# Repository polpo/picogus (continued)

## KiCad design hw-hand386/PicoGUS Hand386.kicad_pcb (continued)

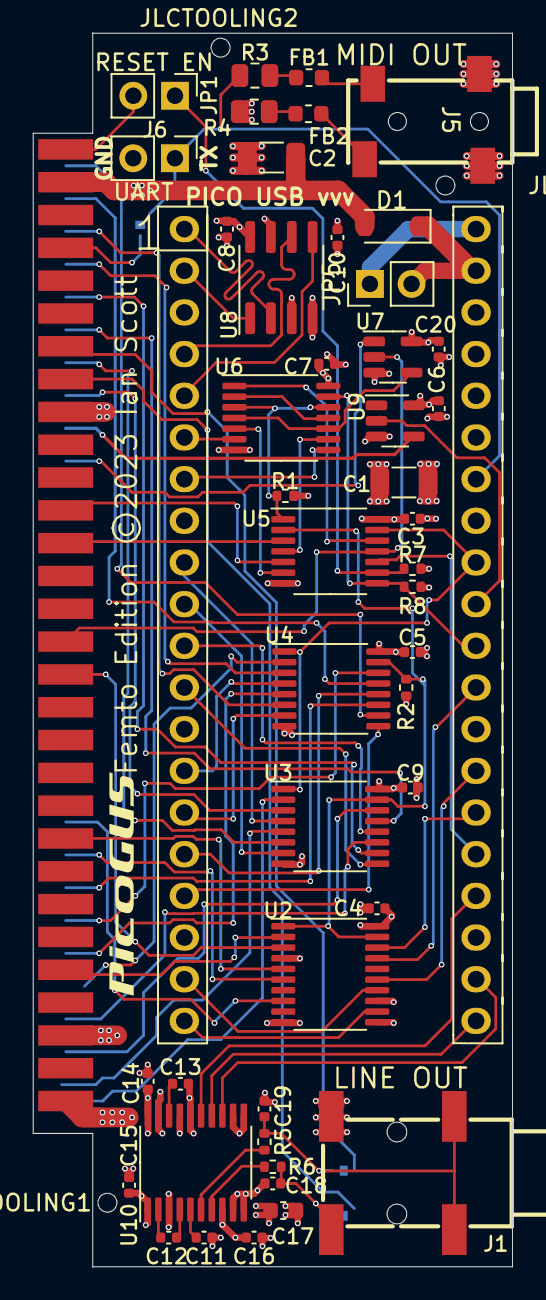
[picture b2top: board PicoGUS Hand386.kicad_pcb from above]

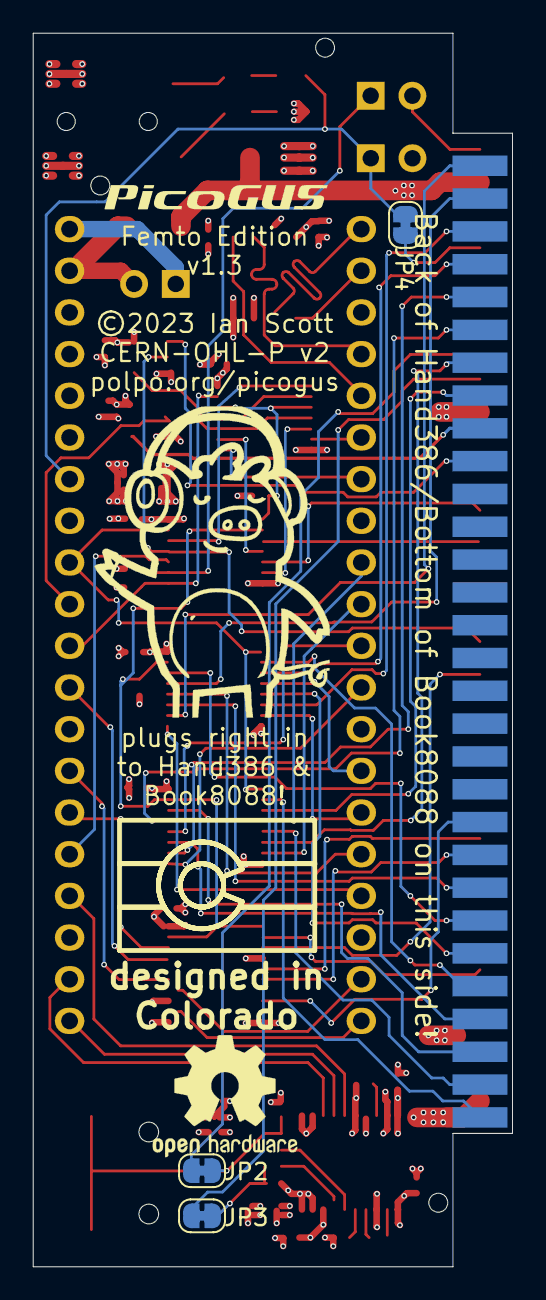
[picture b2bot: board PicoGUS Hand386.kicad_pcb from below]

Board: 4 copper layers, 29.2 x 75.2 mm, 53 parts (3 on the bottom side), 82 nets.

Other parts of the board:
JLCTOOLING1, JLCTOOLING2, JLCTOOLING3: JLCPCB-tooling

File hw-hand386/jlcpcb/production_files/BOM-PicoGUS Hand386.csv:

Comment,Designator,Footprint,LCSC
1K,R8,R_0402_1005Metric,C11702
2.2uF,"C11,C12",C_0402_1005Metric,C12530
PCM5100,U10,TSSOP-20_4.4x6.5mm_P0.65mm,C131154
74AHC14,U5,TSSOP-14_4.4x5mm_P0.65mm,C138310
0.1uF,"C13,C14,C15,C16,C20,C3,C4,C5,C6,C7,C8,C9",C_0402_1005Metric,C1525
SN74CB3T3245,U2,TSSOP-20_4.4x6.5mm_P0.65mm,C15298
2.2nF,"C18,C19",C_0402_1005Metric,C1531
33,R4,R_0805_2012Metric,C161967
10uF,C17,C_0603_1608Metric,C19702
470,"R5,R6",R_0402_1005Metric,C25117
10K,"R1,R2,R7",R_0402_1005Metric,C25744
APS6404L-3SQN-SN,U8,SOIC-8_3.9x4.9mm_P1.27mm,C3028887
1K @ 100MHz,"FB1,FB2",L_0603_1608Metric,C50069
1uF,C10,C_0402_1005Metric,C52923
SN74CB3T3257,"U3,U4",TSSOP-16_4.4x5mm_P0.65mm,C544573
AudioJack3,J5,PJ-231F-4A,C707219
10,R3,R_0805_2012Metric,C728003
74LVC00,U6,TSSOP-14_4.4x5mm_P0.65mm,C7803
74LVC1G00,U7,SOT-23-5,C7826
74LVC1G06,U9,SOT-23-5,C840103
1A 20V Schottky,D1,D_SOD-123,C8598
AudioJack3,J1,PJ-321A,C879743
47uF,"C1,C2",C_1206_3216Metric,C96123
Bus_ISA_8bit,J3,EDGE-60,

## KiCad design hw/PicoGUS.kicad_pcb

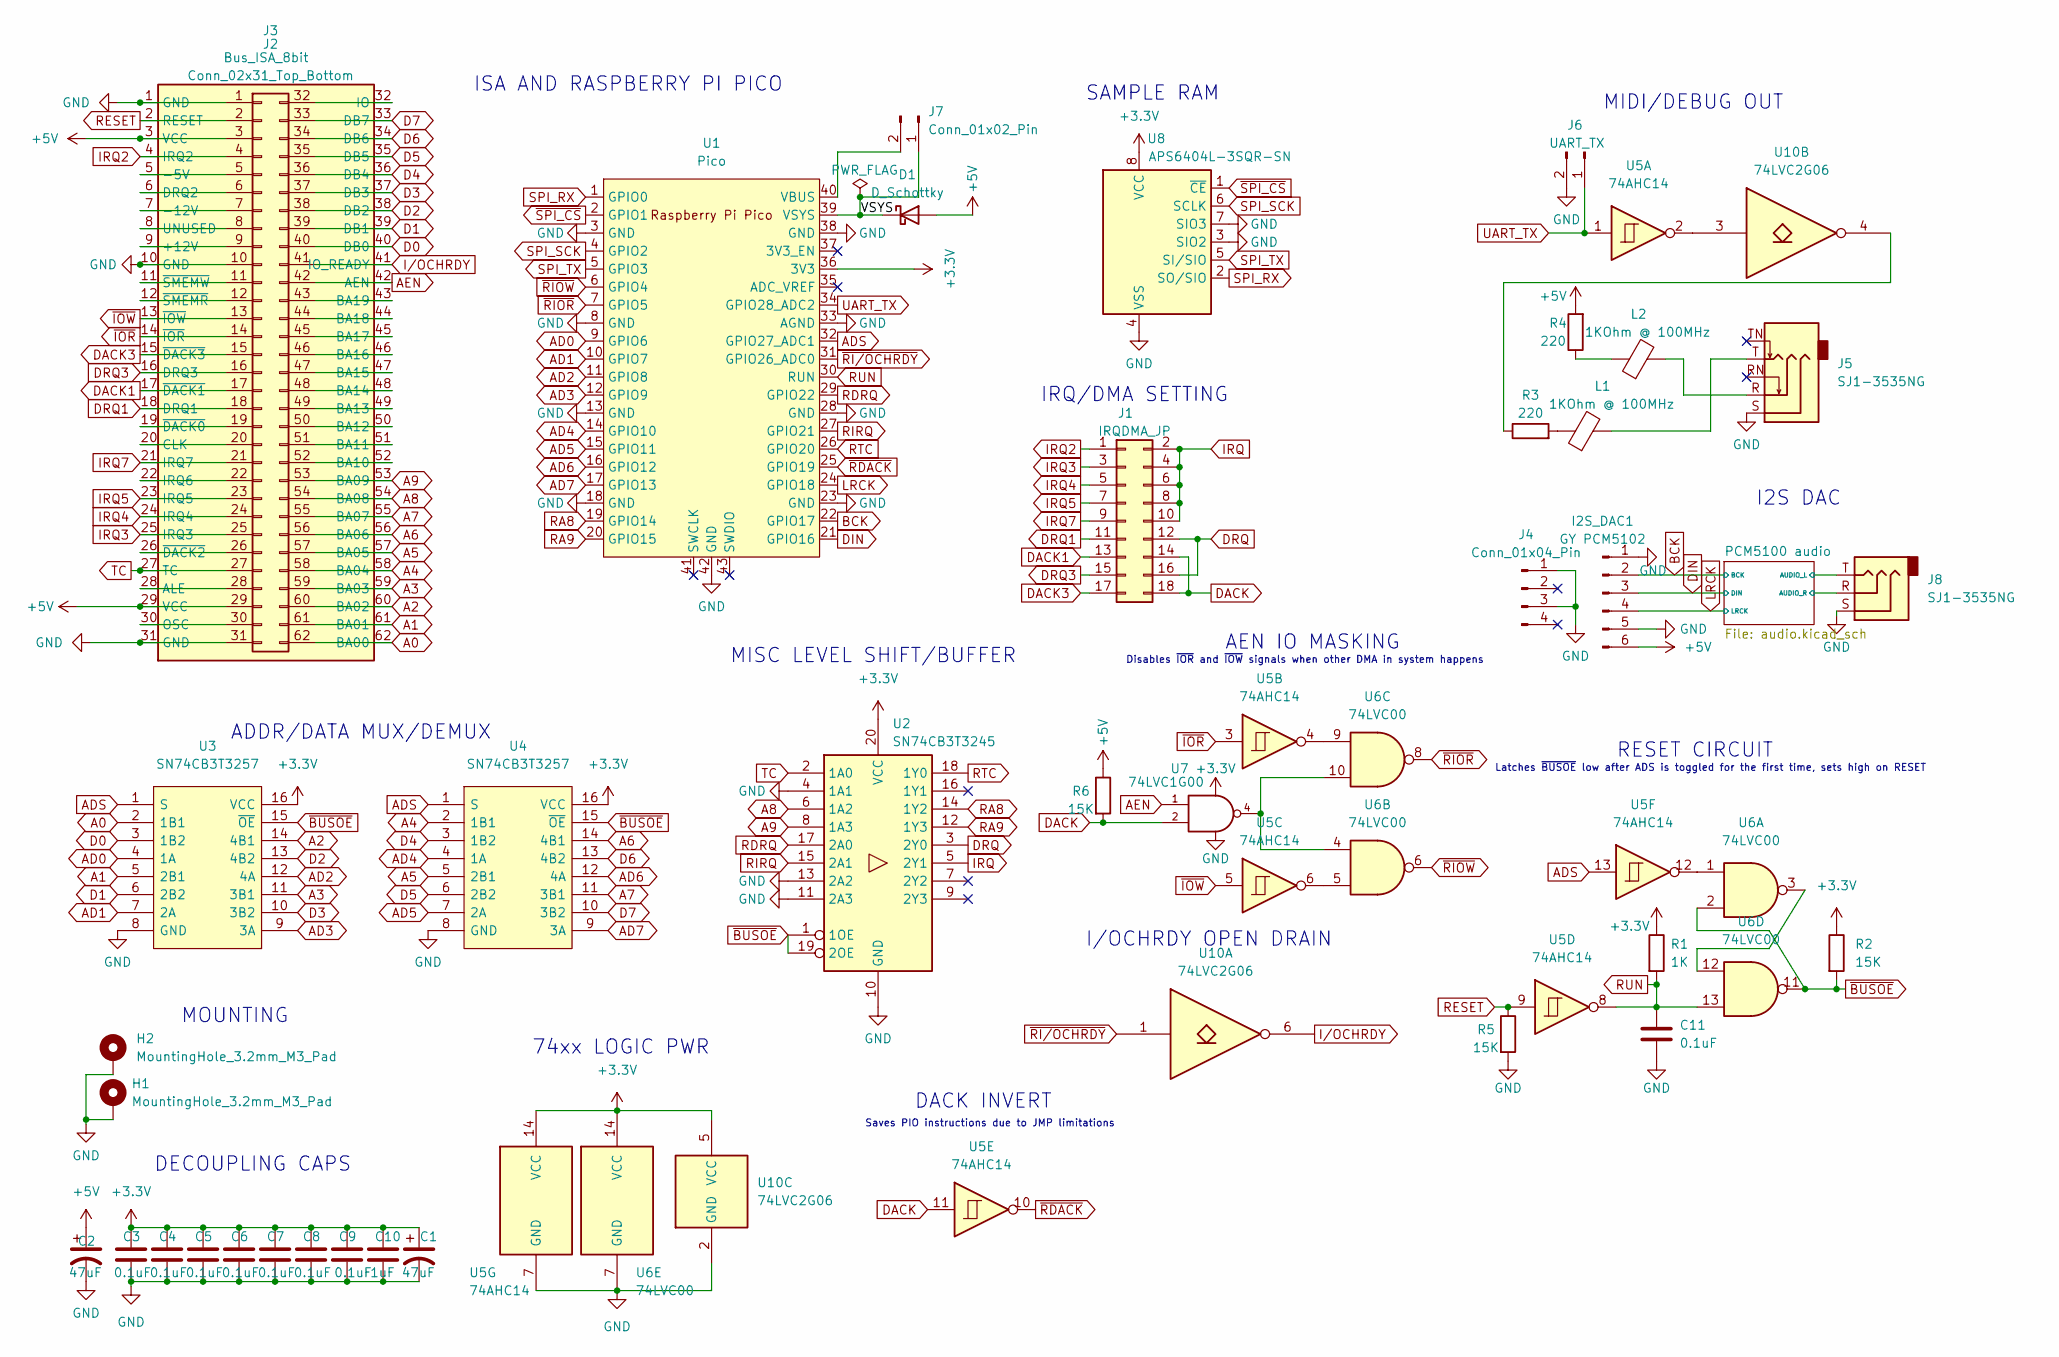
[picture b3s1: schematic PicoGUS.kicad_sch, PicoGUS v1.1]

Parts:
C1, C2: 47uF; C_1206_3216Metric; LCSC C96123
C3, C4, C5, C6, C7, C8, C9, C11: 0.1uF; C_0805_2012Metric; LCSC C49678
C10: 1uF; C_0805_2012Metric; LCSC C28323
D1: D_Schottky; D_SOD-123; LCSC C8598
H1, H2: MountingHole_3.2mm_M3_Pad
I2S_DAC1: GY PCM5102; PinHeader_1x06_P2.54mm_Vertical
J1: IRQDMA_JP; PinHeader_2x09_P2.54mm_Vertical; LCSC C492426
J2: Conn_02x31_Top_Bottom; PinHeader_2x31_P2.54mm_Vertical
J3: Bus_ISA_8bit; BUS_PC_chamfer
J4: Conn_01x04_Pin; PinHeader_1x04_P2.54mm_Vertical
J5, J8: SJ1-3535NG; Jack_3.5mm_CUI_SJ1-3535NG_Horizontal; LCSC C2910528
J6: UART_TX; PinHeader_1x02_P2.54mm_Vertical
J7: Conn_01x02_Pin; PinHeader_1x02_P2.54mm_Vertical
L1, L2: 1KOhm @ 100MHz; L_0805_2012Metric; LCSC C1017
R1: 1K; R_0805_2012Metric; LCSC C17513
R2, R5, R6: 15K; R_0805_2012Metric; LCSC C17475
R3, R4: 220; R_0805_2012Metric; LCSC C5120092
U1: Pico; RPi_Pico_SMD_TH; LCSC C2905423
U2: SN74CB3T3245; TSSOP-20_4.4x6.5mm_P0.65mm; LCSC C15298
U3, U4: SN74CB3T3257; TSSOP-16_4.4x5mm_P0.65mm; Manufacturer_Part_Number 74FST3257DR2G; Mouser Part Number 863-74FST3257DR2G
U5: 74AHC14; SOIC-14_3.9x8.7mm_P1.27mm; LCSC C5510
U6: 74LVC00; SOIC-14_3.9x8.7mm_P1.27mm; LCSC C7802
U7: 74LVC1G00; SOT-23-5; LCSC C7826
U8: APS6404L-3SQR-SN; SOIC-8_3.9x4.9mm_P1.27mm; LCSC C139966
U10: 74LVC2G06; TSOP-6_1.65x3.05mm_P0.95mm; LCSC C548558

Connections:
+5V: C2.1, D1.2 (A), I2S_DAC1.6, J2.3, J2.29, J3.3 (VCC), J3.29 (VCC), R4.2, R6.1
/PCM5100 audio/AUDIO_L: J8.T; also elsewhere on the board
/PCM5100 audio/AUDIO_R: J8.R; also elsewhere on the board
/VSYS: D1.1 (K), J7.1, U1.39 (VSYS)
A0: J2.62, J3.62 (BA00), U3.2 (1B1)
A1: J2.61, J3.61 (BA01), U3.5 (2B1)
A2: J2.60, J3.60 (BA02), U3.14 (4B1)
A3: J2.59, J3.59 (BA03), U3.11 (3B1)
A4: J2.58, J3.58 (BA04), U4.2 (1B1)
A5: J2.57, J3.57 (BA05), U4.5 (2B1)
A6: J2.56, J3.56 (BA06), U4.14 (4B1)
A7: J2.55, J3.55 (BA07), U4.11 (3B1)
A8: J2.54, J3.54 (BA08), U2.6 (1A2)
A9: J2.53, J3.53 (BA09), U2.8 (1A3)
AD0: U1.9 (GPIO6), U3.4 (1A)
AD1: U1.10 (GPIO7), U3.7 (2A)
AD2: U1.11 (GPIO8), U3.12 (4A)
AD3: U1.12 (GPIO9), U3.9 (3A)
AD4: U1.14 (GPIO10), U4.4 (1A)
AD5: U1.15 (GPIO11), U4.7 (2A)
AD6: U1.16 (GPIO12), U4.12 (4A)
AD7: U1.17 (GPIO13), U4.9 (3A)
ADS: U1.32 (GPIO27_ADC1), U3.1 (S), U4.1 (S), U5.13
AEN: J2.42, J3.42 (AEN), U7.1
BCK: I2S_DAC1.2, U1.22 (GPIO17); also elsewhere on the board
D0: J2.40, J3.40 (DB0), U3.3 (1B2)
D1: J2.39, J3.39 (DB1), U3.6 (2B2)
D2: J2.38, J3.38 (DB2), U3.13 (4B2)
D3: J2.37, J3.37 (DB3), U3.10 (3B2)
D4: J2.36, J3.36 (DB4), U4.3 (1B2)
D5: J2.35, J3.35 (DB5), U4.6 (2B2)
D6: J2.34, J3.34 (DB6), U4.13 (4B2)
D7: J2.33, J3.33 (DB7), U4.10 (3B2)
DACK: J1.14, J1.18, R6.2, U5.11, U7.2
DACK1: J1.13, J2.17, J3.17 (~DACK1)
DACK3: J1.17, J2.15, J3.15 (~DACK3)
DIN: I2S_DAC1.3, U1.21 (GPIO16); also elsewhere on the board
DRQ: J1.12, J1.16, U2.3 (2Y0)
DRQ1: J1.11, J2.18, J3.18 (DRQ1)
DRQ3: J1.15, J2.16, J3.16 (DRQ3)
GND: C1.2, C2.2, C3.2, C4.2, C5.2, C6.2, C7.2, C8.2, C9.2, C10.2, C11.2, H1.1, H2.1, I2S_DAC1.1, I2S_DAC1.5, J2.1, J2.10, J2.31, J3.1 (GND), J3.10 (GND), J3.31 (GND), J4.1, J4.3, J5.S, J6.2, J8.S, R5.2, U1.3 (GND), U1.8 (GND), U1.13 (GND), U1.18 (GND), U1.23 (GND), U1.28 (GND), U1.33 (AGND), U1.38 (GND), U1.42 (GND), U2.4 (1A1), U2.10 (GND), U2.11 (2A3), U2.13 (2A2), U3.8 (GND), U4.8 (GND), U5.7 (GND), U6.7 (GND), U7.3 (GND), U8.3 (SIO2), U8.4 (VSS), U8.7 (SIO3), U10.2 (GND); also elsewhere on the board
IRQ: J1.2, J1.4, J1.6, J1.8, J1.10, U2.5 (2Y1)
IRQ2: J1.1, J2.4, J3.4 (IRQ2)
IRQ3: J1.3, J2.25, J3.25 (IRQ3)
IRQ4: J1.5, J2.24, J3.24 (IRQ4)
IRQ5: J1.7, J2.23, J3.23 (IRQ5)
IRQ7: J1.9, J2.21, J3.21 (IRQ7)
I/OCHRDY: J2.41, J3.41 (IO_READY), U10.6
LRCK: I2S_DAC1.4, U1.24 (GPIO18); also elsewhere on the board
unnamed: J2.5, J3.5 (-5V)
unnamed: J2.6, J3.6 (DRQ2)
unnamed: J2.7, J3.7 (-12V)
unnamed: J2.8, J3.8 (UNUSED)
unnamed: J2.9, J3.9 (+12V)
unnamed: J2.11, J3.11 (~SMEMW)
unnamed: J2.12, J3.12 (~SMEMR)
unnamed: J2.19, J3.19 (~DACK0)
unnamed: J2.20, J3.20 (CLK)
unnamed: J2.22, J3.22 (IRQ6)
unnamed: J2.26, J3.26 (~DACK2)
unnamed: J2.28, J3.28 (ALE)
unnamed: J2.30, J3.30 (OSC)
unnamed: J2.32, J3.32 (IO)
unnamed: J2.43, J3.43 (BA19)
unnamed: J2.44, J3.44 (BA18)
unnamed: J2.45, J3.45 (BA17)
unnamed: J2.46, J3.46 (BA16)
unnamed: J2.47, J3.47 (BA15)
unnamed: J2.48, J3.48 (BA14)
unnamed: J2.49, J3.49 (BA13)
unnamed: J2.50, J3.50 (BA12)
unnamed: J2.51, J3.51 (BA11)
unnamed: J2.52, J3.52 (BA10)
unnamed: J5.R, L2.2
unnamed: J5.T, L1.2
unnamed: J7.2, U1.40 (VBUS)
unnamed: L1.1, R3.2
unnamed: L2.1, R4.1
unnamed: R3.1, U10.4
unnamed: U5.4, U6.9
unnamed: U5.6, U6.5
unnamed: U5.12, U6.1
unnamed: U6.4, U6.10, U7.4
unnamed: U6.3, U6.12
unnamed: U5.2, U10.3
RA8: U1.19 (GPIO14), U2.14 (1Y2)
RA9: U1.20 (GPIO15), U2.12 (1Y3)
RDRQ: U1.29 (GPIO22), U2.17 (2A0)
RESET: J2.2, J3.2 (RESET), R5.1, U5.9
RIRQ: U1.27 (GPIO21), U2.15 (2A1)
RTC: U1.26 (GPIO20), U2.18 (1Y0)
RUN: C11.1, R1.2, U1.30 (RUN), U5.8, U6.13
SPI_RX: U1.1 (GPIO0), U8.2 (SO/SIO)
SPI_SCK: U1.4 (GPIO2), U8.6 (SCLK)
SPI_TX: U1.5 (GPIO3), U8.5 (SI/SIO)
TC: J2.27, J3.27 (TC), U2.2 (1A0)
UART_TX: J6.1, U1.34 (GPIO28_ADC2), U5.1
~BUSOE: R2.2, U2.1 (1OE), U2.19 (2OE), U3.15 (~OE), U4.15 (~OE), U6.2, U6.11
~IOR: J2.14, J3.14 (~IOR), U5.3
~IOW: J2.13, J3.13 (~IOW), U5.5
~RDACK: U1.25 (GPIO19), U5.10
~RIOR: U1.7 (GPIO5), U6.8
~RIOW: U1.6 (GPIO4), U6.6
~RI/OCHRDY: U1.31 (GPIO26_ADC0), U10.1
~SPI_CS: U1.2 (GPIO1), U8.1 (~CE)

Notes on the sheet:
Saves PIO instructions due to JMP limitations
DECOUPLING CAPS
I2S DAC
Disables ~{IOR} and ~{IOW} signals when other DMA in system happens
Latches ~{BUSOE} low after ADS is toggled for the first time, sets high on RESET
MIDI/DEBUG OUT
MOUNTING
MISC LEVEL SHIFT/BUFFER
IRQ/DMA SETTING
DACK INVERT
ADDR/DATA MUX/DEMUX
SAMPLE RAM
AEN IO MASKING
ISA AND RASPBERRY PI PICO
RESET CIRCUIT
I/OCHRDY OPEN DRAIN
74xx LOGIC PWR

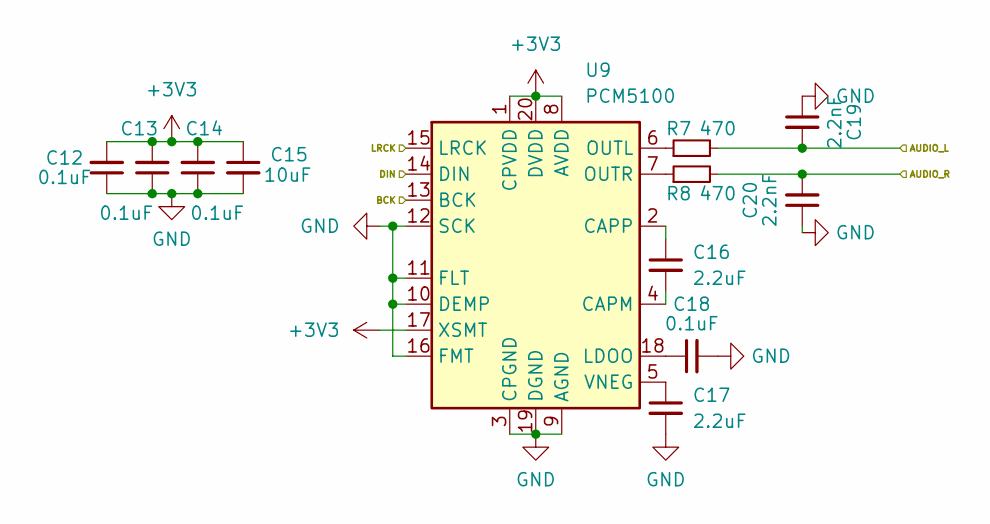
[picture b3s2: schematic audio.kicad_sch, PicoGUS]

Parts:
C12, C13, C14, C18: 0.1uF; C_0805_2012Metric
C15: 10uF; C_0805_2012Metric
C16, C17: 2.2uF; C_0805_2012Metric
C19, C20: 2.2nF; C_0805_2012Metric
R7, R8: 470; R_0805_2012Metric
U9: PCM5100; TSSOP-20_4.4x6.5mm_P0.65mm

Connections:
/PCM5100 audio/AUDIO_L: C19.2, R7.2; also elsewhere on the board
/PCM5100 audio/AUDIO_R: C20.2, R8.2; also elsewhere on the board
BCK: U9.13 (BCK); also elsewhere on the board
DIN: U9.14 (DIN); also elsewhere on the board
GND: C12.1, C13.1, C14.1, C15.2, C17.2, C18.2, C19.1, C20.1, U9.3 (CPGND), U9.9 (AGND), U9.10 (DEMP), U9.11 (FLT), U9.12 (SCK), U9.16 (FMT), U9.19 (DGND); also elsewhere on the board
LRCK: U9.15 (LRCK); also elsewhere on the board
unnamed: C16.2, U9.4 (CAPM)
unnamed: C16.1, U9.2 (CAPP)
unnamed: C18.1, U9.18 (LDOO)
unnamed: R7.1, U9.6 (OUTL)
unnamed: R8.1, U9.7 (OUTR)
unnamed: C17.1, U9.5 (VNEG)

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
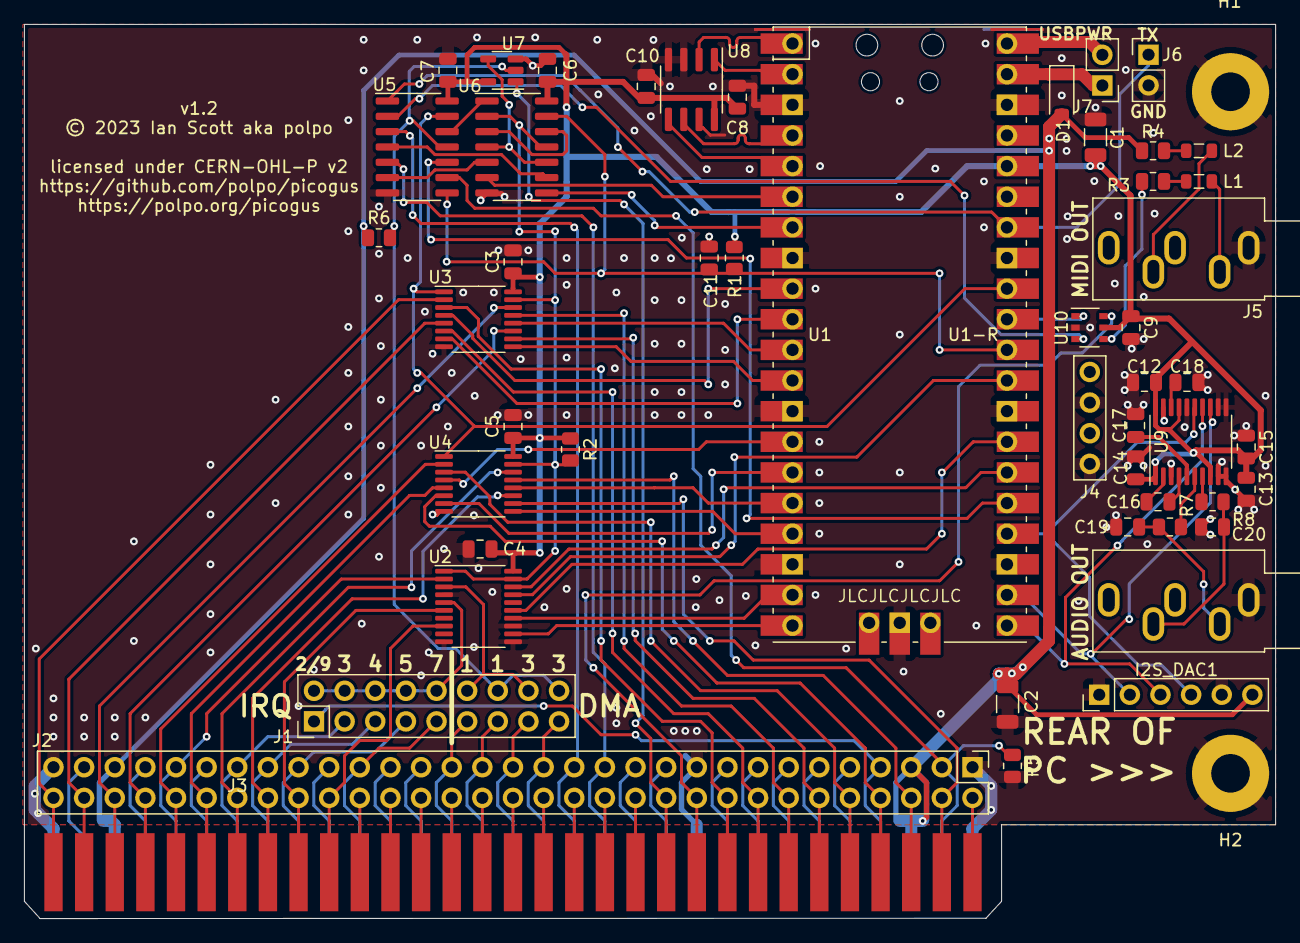
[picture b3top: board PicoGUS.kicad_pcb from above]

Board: 2 copper layers, 103.7 x 74.1 mm, 53 parts (0 on the bottom side), 112 nets.

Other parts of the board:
U1-R: GHOST-20P; Ghost-20P

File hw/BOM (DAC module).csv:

Mfr. #,Manufacturer,Qty,Mouser #,Digi-Key #,LCSC #,Customer #,Footprint,Description,Notes
CL31A476MPHNNNE,Samsung Electro-Mechanics ,2,187-CL31A476MPHNNNE,1276-3063-1-ND,C96123,"C1,C2",0805,47 µF ±20% 10V Ceramic Capacitor X5R 1206 (3216 Metric),Subst any 47uF electrolytic cap w/ 2mm lead spacing
CL21B105KBFNNNE,Samsung Electro-Mechanics ,1,187-CL21B105KBFNNNE,1276-1029-1-ND,C28323,C10,0805,1 µF ±10% 50V Ceramic Capacitor X7R 0805 (2012 Metric),Subst any X7R 1uF 0805 ceramic cap
CL21B104KCFNNNE,Samsung Electro-Mechanics ,8,187-CL21B104KCFNNNE,399-C0805C104M5RAC7800CT-ND,C28233,"C3,C4,C5,C6,C7,C8,C9,C11",0805,0.1 µF ±10% 100V Ceramic Capacitor X7R 0805 (2012 Metric),Subst any X7R 0.1uF 0805 ceramic cap
B5819W-TP,Micro Commercial Components,1,833-B5819W-TP,B5819W-TPMSCT-ND,C8598,D1,SOD-123, 40V 600mV@1A 1A SOD-123 Schottky Barrier Diodes (SBD),Subst any 1A 20V Schottky SOD123 diode
M20-9771246,Harwin,1,855-M20-9771246,M20-9771246-ND,C2840012,"I2S_DAC1,J4,J7",,Headers & Wire Housings 12 SIL VERTICAL PIN HEADER TIN,"Cut into 6, 4, 2 pin sections"
10129381-918001BLF,FCI / Amphenol,1,649-1012938191801BLF,609-10129381-918001BLF-ND,C2935925,J1,PinHeader_2x09_P2.54mm_Vertical,Headers & Wire Housings HEADER DR VT TH 2X9-10129381-918001BLF,Subst any 2x9 2.54mm pin header
SJ1-3535NG,CUI Devices,1,490-SJ1-3535NG,CP1-3535NG-ND,C5372857 ,J5,Jack_3.5mm_CUI_SJ1-3535NG_Horizontal,"3.50mm (0.141"", 1/8"", Mini Plug) - Headphone Phone Jack Stereo (3 Conductor, TRS) Connector Solder","Black jack for MIDI - Yellow jacks on AliExpress, search PJ-325"
PH1-02-UA,Adam Tech,1,649-54102-T0800LF,2057-PH1-02-UA-ND,C2883961,J7,PinHeader_1x02_P2.54mm_Vertical,"Connector Header Through Hole 2 position 0.100"" (2.54mm)",
SJ1-3535NG-GR,CUI Devices,1,490-SJ1-3535NG-GR,SJ1-3535NG-GR,C692438,J8,Jack_3.5mm_CUI_SJ1-3535NG_Horizontal,"3.50mm (0.141"", 1/8"", Mini Plug) - Headphone Phone Jack Stereo (3 Conductor, TRS) Connector Solder, green",Green jack for line out
BLM21AG102SN1D,Murata Electronics ,2,81-BLM21AG102SN1,490-1041-1-ND,C85835,"FB1,FB2",0805,1 kOhms @ 100 MHz 1 Ferrite Bead 0805 (2012 Metric) 600mA 280mOhm,Subst any 1kOhm @ 100Mhz 0805 ferrite bead
CR0805-JW-102ELF,Bourns,1,652-CR0805JW-102ELF,CR0805-JW-102ELFCT-ND,C17513,R1,0805,"1 kOhms ±5% 0.125W, 1/8W Chip Resistor 0805 (2012 Metric) Moisture Resistant Thick Film",Subst any 1kOhm 0.125w 0805 resistor
CR0805-JW-153ELF,Bourns,3,652-CR0805JW-153ELF,118-CR0805-JW-153ELFCT-ND,C17475,"R2,R5,R6",0805,"15 kOhms ±5% 0.125W, 1/8W Chip Resistor 0805 (2012 Metric) Moisture Resistant Thick Film",Subst any 15kOhm 0.125w 0805 resistor
RK73B2ATTD221J,KOA Speer,2,660-RK73B2ATTD221J,2019-RK73B2ATTD221JCT-ND,C5120092,"R3,R4",0805,"220 Ohms ±5% 0.25W, 1/4W Chip Resistor 0805 (2012 Metric) Automotive AEC-Q200 Thick Film",Subst any 220Ohm 0.25w 0805 resistor
CR0805-JW-471ELF,Bourns,2,652-CR0805JW-471ELF,118-CR0805-JW-471ELFCT-ND,C17710,"R7,R8",0805,"470 Ohms ±5% 0.125W, 1/8W Chip Resistor 0805 (2012 Metric) Moisture Resistant Thick Film",Subst any 470Ohm 0.125w 0805 resistor
SC0915 ,Raspberry Pi,1,358-SC0915,2648-SC0915CT-ND,C2905423,U1,,Single Board Computers Raspberry Pi Pico,Pico W and Pico H also work
"74LVC244APW,118",Nexperia,1,771-74LVC244APW-T,1727-2875-1-ND,C6079,U2,TSSOP-20,"Buffer, Non-Inverting 2 Element 4 Bit per Element 3-State Output 20-TSSOP",
SN74CB3T3257,Texas Instruments,2,595-SN74CB3T3257PWR,296-17850-1-ND,C544573,"U3,U4",TSSOP-14,"Encoders, Decoders, Multiplexers & Demultiplexers 4-Bit 1-OF-2 FET Mltplx/Demultplxr",
74AHC14S14-13,Diodes Incorporated,1,621-74AHC14S14-13,31-74AHC14S14-13CT-ND,C6942,U5,SOIC-14,Inverter IC 6 Channel Schmitt Trigger 14-TSSOP,Subst any 74LVC14
74LVC00AS14-13,Diodes Incorporated,1,621-74LVC00AS14-13,31-74LVC00AS14-13CT-ND,C526338,U6,SOIC-14,NAND Gate IC 4 Channel 14-SO,Subst any 74LVC00
SN74LVC1G00DBVR,Texas Instruments,1,595-SN74LVC1G00DBVR,74LVC1G00W5-7DICT-ND,C7826,U7,SOT-23-5,Logic Gates 2-Input,Subst any 74LVC1G00
APS6404L-3SQR-SN,AP Memory Technology,1,878-APS6404L-3SQR-SN,1528-4677-ND,C139966,U8,SOIC-8,"DRAM IoT RAM 64Mb QSPI (x1,x4) SDR 133/84MHz, RBX, 3V, Ind. Temp., SOP8","Subst Adafruit 4677, Vilsion Tech VTI7064MSME, ISSI IS66WVS1M8BLL-104NLI, IPUS IPS6404, Lyontek LY68L6400SLIT, Espressif ESP-PSRAM64H"
SN74LVC2G06DBVR,Texas Instruments,1,595-SN74LVC2G06DBVR,296-13492-1-ND,C402162,U10,SOT-23-6,Buffers & Line Drivers Single Invert w/OD,Subst any 74LVC1G06

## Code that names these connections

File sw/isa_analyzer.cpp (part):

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    // Configure bus input pins: enable input, disable isolation (RP2350 requirement),
    // and disable pulls. Without this, PIO reads all zeros.
    const int bus_pins[] = {
        IOW_PIN, IOR_PIN,                           // control signals
        AD0_PIN, AD0_PIN+1, AD0_PIN+2, AD0_PIN+3,  // AD0-AD9
        AD0_PIN+4, AD0_PIN+5, AD0_PIN+6, AD0_PIN+7,
        AD0_PIN+8, AD0_PIN+9,
        DACK_PIN, TC_PIN,                           // DMA signals
    };
    for (int pin : bus_pins) {
        gpio_set_input_enabled(pin, true);
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
    // Waggle ADS to set BUSOE latch (enable bus transceivers)
    puts("Enabling bus transceivers...");
    gpio_init(ADS_PIN);
    gpio_set_dir(ADS_PIN, GPIO_OUT);
    gpio_put(ADS_PIN, 1);
    busy_wait_ms(10);
    gpio_put(ADS_PIN, 0);

    gpio_set_slew_rate(ADS_PIN, GPIO_SLEW_RATE_FAST);

    // Configure PIO
    puts("Starting ISA bus PIO...");
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
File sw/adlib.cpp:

/**
 * Copyright (c) 2020 Raspberry Pi (Trading) Ltd.
 *
 * SPDX-License-Identifier: BSD-3-Clause
 */

#include <stdio.h>
#include <math.h>

#if PICO_ON_DEVICE

#include "hardware/clocks.h"
#include "hardware/structs/clocks.h"

#endif

#include "pico/stdlib.h"

#include "pico/audio_i2s.h"

#include "opl.h"

#if PICO_ON_DEVICE
#include "pico/binary_info.h"
bi_decl(bi_3pins_with_names(PICO_AUDIO_I2S_DATA_PIN, "I2S DIN", PICO_AUDIO_I2S_CLOCK_PIN_BASE, "I2S BCK", PICO_AUDIO_I2S_CLOCK_PIN_BASE+1, "I2S LRCK"));
#endif

#define SAMPLES_PER_BUFFER 64

struct audio_buffer_pool *init_audio() {

    static audio_format_t audio_format = {
            .sample_freq = 49716,
            .format = AUDIO_BUFFER_FORMAT_PCM_S16,
            .channel_count = 2,
    };

    static struct audio_buffer_format producer_format = {
            .format = &audio_format,
            .sample_stride = 4
    };

    struct audio_buffer_pool *producer_pool = audio_new_producer_pool(&producer_format, 2,
                                                                      SAMPLES_PER_BUFFER); // todo correct size
    bool __unused ok;
    const struct audio_format *output_format;
    struct audio_i2s_config config = {
            .data_pin = PICO_AUDIO_I2S_DATA_PIN,
            .clock_pin_base = PICO_AUDIO_I2S_CLOCK_PIN_BASE,
            .dma_channel = 6,
            .pio_sm = 1,
    };

    output_format = audio_i2s_setup(&audio_format, &config);
    if (!output_format) {
        panic("PicoAudio: Unable to open audio device.\n");
    }

    //ok = audio_i2s_connect(producer_pool);
    ok = audio_i2s_connect_extra(producer_pool, false, 0, 0, NULL);
    assert(ok);
    audio_i2s_set_enabled(true);
    return producer_pool;
}

extern "C" void OPL_Pico_Mix_callback(audio_buffer_t *);

void play_adlib() {
    puts("starting core 1");
    uint32_t start, end;

    struct audio_buffer_pool *ap = init_audio();
    for (;;) {
        struct audio_buffer *buffer = take_audio_buffer(ap, true);
        OPL_Pico_Mix_callback(buffer);
        // putchar((unsigned char)buffer->buffer->bytes[1]);
        give_audio_buffer(ap, buffer);
    }
}

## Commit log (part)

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2024-01-04 increase i2s audio buffer for/during testing.
2024-01-04 work in progress commit
2024-01-04 Add STL files for Femto edition case
    Design is courtesy (c) FireTwoOneNine.
2024-01-13 Clock speed and memory layout tweaks
2024-01-15 Increase CLKDIV for IOW because 5170 doesn't have valid data for 30ns
2024-01-15 gitignore vscode folder
2024-01-16 Update to use new DMA PIO
2024-01-24 Firmware v1.0.2
2024-01-26 Update to reduce digital volume level (to be improved later)
2024-02-20 move to 10 bit fractional delta
2024-03-17 Software configurable 44k force
2024-03-19 Update pgusinit for fixed 44.1kHz output
2024-03-19 Update changelog; new versions
2024-03-19 Update rp2040-psram
2024-03-24 Don't busy wait for sysex delay
2024-03-26 "Bufferless" SB mixing
2024-03-26 Fix issues in pgusinit interface
2024-03-26 Add DSP_DIRECT_DAC mode
2024-03-26 Rename adlibplay to sbplay
2024-03-26 Use command buffer for OPL
2024-03-26 Reorganize into new SB mode
2024-03-27 Config OPL wait; allow WT volume; inline in sbdsp
2024-03-29 sbdsp: Add speaker enable/disable commands
2024-04-22 Add S/PDIF optical output to board
2024-04-26 spdif experiment
2024-04-27 Get working on RP2350
2024-04-27 Implementation of multi-firmware for PicoGus.
    Flash only one file: pg-multi.uf2 only one time. It contains all firmwares (6 at this moment). You can change between them in DOS:
    New usage for this version:
    pgusinit /m x [d] - change card mode to x (1=gus,2=sb,3=mpu,4=tandy,5=cms,6=joy)
    the optional parameter 'd' makes the mode permanent at boot
    (Only if pg-multi.uf2 is flashed)
    Examples of use:
2024-05-04 Try out ymfm
2024-05-04 Align firmwares on 1k boundaries
2024-05-04 Exclude generated files from git
2024-05-27 Non-working storing of settings in flash
2024-06-05 Update emu8950.c
    Fix bug where attack step 0 for eg_rate_h 15 causing envelop never switch to decay, causing some music missing notes in higher notes.
2024-06-15 Update emu8950.c
    remove spaces from last commit
2024-06-30 Working multifw build within cmake
2024-06-30 Build multifw in GH action
2024-06-30 Don't use LTO on bootloader
2024-06-30 Add settings save to pgusinit
2024-06-30 Add missing hw files
2024-07-01 derive RX byte interval from protocol max bytes per packet, add license
2024-07-06 Update submodules
2024-07-06 Dynamic PIC timers
2024-07-07 Fixes for pgusinit
2024-07-07 Pin GH workflow to ubuntu-22.04 just in case
2024-07-07 Mouse working in CMS/Tandy/AdLib modes
2024-07-07 Fix bool option setting and add xinput driver install callback
2024-07-08 Remove release script - it's currently all done in CMake and GH Actions
2024-07-14 Simultaneous MPU + SB/GUS
2024-07-25 Kind of working dual OPL2 playback using EMU8950_LINEAR/SLOT_RENDER
2024-07-27 Simultaneous MPU with most modes
2024-07-30 Updates to pgusinit for simultaneous MPU
2024-07-30 Remove extra spaces in pgusinit help
2024-08-17 Move tinyusb and tusb_xinput into lib dir
2024-08-22 Don't use LTO
2024-08-23 Add NE2k help and recognize NE2000_MODE in pgusinit
2024-10-26 SB: Fix Tyrian and Dig-It! by implementing DSP_DAC_PAUSE_DURATION
2024-11-23 Fix STMIK's wonky SB detection
2024-11-23 Fix setting port numbers to less than 0xff or ending with 0x00
2024-11-28 License housekeeping
2024-12-01 Move to non-poll for wifi
2024-12-01 Fix build
2024-12-04 Drop flash_safe_execute_core_init as it interferes with cyw43
2024-12-09 Clean up MPU-401, increase midi buffer size in non-MPU modes
2024-12-09 Temporarily use develop branch of Pico SDK to bring in timer fix
    Fixes issue introduced in SDK 2.1.0, reported in pico-sdk issue 2118:
    https://github.com/raspberrypi/pico-sdk/issues/2118
2024-12-15 Work in progress SB16 lite support
2024-12-20 Track drq for status bit
2024-12-25 WSS PIO playback WIP checkpoint
2025-01-04 WSS cleanup
2025-03-16 Exit pgusinit when card not detected instead of carrying on
2025-03-17 Prep for XIP PSRAM support
2025-03-17 Better RP2350 configurability
2025-05-21 Better support for CD/SB
2025-06-13 Pull wbcbz7's tinyusb branch in as submodule, vendor fatfs
2025-06-13 Fix adlib build
2025-06-13 Working CD audio in USB mode
2025-06-13 CD image handling
2025-06-13 use simple callback with sb
2025-06-15 Optionally auto-advance image on USB reinsert
2025-06-15 Simplify: single cdrom and fatfs instance, better support single USB drive
2025-06-17 Simplify audio_fifo for sbdsp
2025-06-18 Better handling of CD image load errors
2025-06-19 Consolidate Tandy and CMS into PSG mode
2025-06-19 Fix selecting wrong mode in pgusinit
2025-06-19 Bump pgusinit and protocol version
2025-06-19 Fix wiki link in CHANGELOG
2025-06-19 Fix MIDI output in SB and USB modes
2025-06-22 Many fixes/improvements to CD image handling:
    - Fix memory leak when changing images (file handle not freed)
    - Longer max file length limit (127 chars)
    - Better errors when USB not present
    - Fix polling of CD status register when listing images
    - Add ability to load image by name
    - Many weird edge cases with image loading state fixed
2025-06-22 Add /loadname to pgusinit usage, update pgusinit README
2025-06-30 Volume control
2025-07-04 Iterative command parser
    Refactored the inline argument commands into functions that iterate through a command table. This should help make input commands more robust and easier to expand.
    It also allows for default values when setting options. For example if the user wants a default value for the OPL port, they can use "/oplport default".
    Since /sbport and /gusport always check the environment for SET BLASTER and SET ULTRASND, I added the function for pgusinit to retrieve these values from the environment directly. This could open up 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
    The commands should behave exactly as I did when they were inline to start, but can now easily
2025-07-04 ctrlGet commands, cleanup printf feedback
2025-07-04 Print status functions
    More clean up to main(). I am finding there is some overlap with the term "mode" which indicates the global card mode (ex. SB_MODE, GUS_MODE, etc) as well as register modes communicating with PicoGUS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
2025-07-04 Remove unused variables
2025-07-06 Remove no commands check
2025-07-06 Fix /cdvol
2025-07-07 Consolidate all volume printf to printVolume()
2025-07-14 Initialize with set_volume()
    Restores volume settings with mode changes and resets.
2025-07-29 More optimization
2025-07-30 OPL command buffer has race condition now, disable
2025-07-30 Add link to vswitchzero video
2025-08-07 pgusinit quality of life improvements:
    Restoration of prior pgusinit functionality:
    - Case insensitive command line switches
    - Bail out if there are errors detecting the card
    - Bail out on firmware mismatch, but allow flashing new firmware
    More QoL improvements:
    - Generic paging interface that detects rows on screen
2025-08-08 Make scale_sample inline
2025-08-08 Volume scaling for bufferless_ng sbplay
2025-08-08 Project directory reorg
2025-08-08 Clean up unused OPL2 detritus
2025-08-09 Apply audio taper to volume setting
2025-08-09 More pgusinit refactor
2025-08-09 Send more midi bytes each loop
2025-08-09 Migrate old settings in flash
2025-08-26 pgusinit: fix bug where port is parsed as decimal
2025-08-26 pgusinit: restore /defaults command
2025-10-02 Squash rp2350
2026-03-17 "Pull" based DMA for SB - doesn't require DMA interval dithering
2026-03-17 Remove old non-bufferless code
2026-03-18 ISA analyzer: capture+flush in a loop
2026-03-18 try to prevent pops in single-cycle mode
2026-03-19 SB: speaker control should only mute output and do not stop DMA
    (fixes Scream Tracker 3)
2026-03-19 SB: emulate DSP I/O port address aliasing
2026-03-20 SB: mixer volume control inital implementation
2026-03-20 SB: implement mixer Output Switch (0x3C) register
2026-03-21 SB: mixer locking and time constant fixup options
2026-03-21 SB: finalize IRQ/DMA/options settings
2026-03-21 SB: clock down DMA PIO, minor sbdsp_set_type() fix
2026-03-21 SB: reset more stuff, fix TC-related oversight
2026-03-23 SB: move dsp_process() to second core, tweak DSP reset procedure
2026-03-23 SB: remove wait for DACK deassertion in dma_write_multi
    (makes it work in DMA controller demand mode - fixes Unreal/FC in SBPro mode)
2026-03-25 SB: fix reentrancy issues
2026-03-28 Revert "temp overclock UART to 2 Mbps"
    This reverts commit 0e88976b60c6c8cca25c8f637c6c0056444174a3.
2026-03-28 opl: enable EMU8950 TLL via pre-computed table in flash (.flashdata section)
    The TLL (Total Level Lookup) table is 128KB — too large for the RP2040's
    256KB RAM when the firmware also runs code from RAM. Previous attempts to
    use a `const` array failed because the firmware uses a copy_to_ram binary
    type, which copies ALL sections including `.rodata` into RAM at boot.
    The fix: place the pre-computed table in the `.flashdata.tll_table` linker
    section. Both pico-sdk's `memmap_copy_to_ram.ld` and the local
2026-03-28 resampler: resolve python path
2026-03-28 cdrom: add memory barrier before setting CD_STATUS_PLAYING
    Ensures seek_pos, cd_end, and fifo_reset are all visible to core 1 before cd_status is set to PLAYING, preventing core 1 from starting audio consumption against a partially-updated state.
2026-03-28 fix(cdrom): recover from error state on /cdlist; fix image path edge cases
    CMD_CDLIST now queues image list when status is ERROR, not just IDLE,
    fixing permanent stuck state after a failed /cdload or /cdloadname
    isCDImage: fix len<=4 guard so ".iso"/".cue" are rejected; hide all
    dot-files instead of only macOS ._-prefixed files
    Replace strcpy with strncpy for image_path to prevent buffer overrun
2026-03-28 Update versioning v3.3.0-beta
2026-03-28 cdrom: USB/FAT stability fixes
    Fixes three reliability issues in msc_app.c:
    Add 2-second timeout to wait_for_disk_io() to prevent firmware lockup when a USB drive stops responding mid-transfer
    Propagate SCSI errors from disk_io_complete() — disk_read()/disk_write() now return RES_ERROR on failure instead of always returning RES_OK
    Guard tuh_msc_umount_cb() against a second MSC device disconnect tearing down the active drive's filesystem
2026-03-28 fix(opl): fix OPL Timer 2 enable writing to timer1.enabled instead of timer2.enabled
    In OPL_Pico_WriteRegister(), the register 0x04 (TIMER_CTRL) handler
    had a copy-paste error in the Timer 2 enable path: it wrote the Timer 2
    start bit (0x02) into timer1.enabled instead of timer2.enabled.
    This meant timer2.enabled was always 0, so OPLTimer_CalculateEndTime()
    never set timer2.expire_time, and the status register port read never
    set bit 5 (Timer 2 expired). The bug also had a secondary effect:
2026-03-28 fix(opl): eliminate cross-core OPL struct race via OPL_CMD_BUFFER
    This was an audible in games like Doom. It would cause an occasional small interruption when picking up items.
    Core 0 (bus ISR) was calling OPL_writeReg() directly on the emu8950
    OPL struct while Core 1 was simultaneously reading it in OPL_calc_buffer()
    to generate audio. With no synchronization between the cores, a register
    write landing mid-calculation produces torn state — a mix of old and new
    operator fields — causing occasional clicks or pops during OPL music.
2026-03-28 fix(audio): fix samples_in_fifo race between core 1 main loop and PWM ISR
    fifo_add_sample() increments samples_in_fifo with a non-atomic
    load-add-store. The PWM ISR (audio consumer) runs on the same core
    and can preempt the main loop (OPL producer) between the load and
    store, decrementing the counter mid-update. The ISR's decrement is
    then overwritten by the main loop's store, inflating samples_in_fifo
    by 1. Over time this drift could cause the producer to throttle itself
2026-03-28 Improve OPL synthesis quality
2026-03-29 Implement audio_fifo as lock-free SPSC queue to not require disabling interrupts
2026-03-29 Refactor polyphase resampler to allow for stereo resampling
2026-03-29 Clamp with hardware interpolator
2026-03-29 Bring in some changes from 86box to support default win9x MKE driver
2026-03-29 Overclock at runtime instead of at start to help stability on marginal boards
2026-03-30 Support variable output sample rate w/ new IRQ-driven output for GUS
2026-03-30 Boost OPL volume 1.5X
2026-03-31 Fix Miles AIL detection of SB16
2026-04-01 SB: add missing DSP_CONTINUE_DMA_16 (0xD6) command and fix names of other DMA pause/continue commands
2026-04-04 Disable hardware clamp in dbopl - there's races due to it being used in multiple places
2026-04-04 HW interpolator for SB
2026-04-06 emu8950 process
2026-04-06 Firmware v4.0.0-beta
2026-04-10 fixed typo that passes irq instead of DMA
2026-04-13 Add SB16/Pro compatibility
2026-04-14 Revert "protocol == 1 it's never reached because b is never == 512"
2026-04-14 SB: add fake ADC
2026-04-14 Better messaging when BLASTER has problems
2026-04-14 MPU: use 256 byte MIDI output buffer like real MPU-401
2026-04-14 MPU: fix sysex delay - it's in ms, not us
2026-04-14 pgusinit general fixes
2026-04-14 MKE: enlarge sector buffer that audio sectors land in during playback
2026-04-14 Firmware v4.1.0
2026-04-17 Fix printf panic in GUS mode
2026-04-18 Fix GUS playmidi - it uses both timers
2026-04-18 Firmware v4.1.1-beta.0
2026-04-20 SB: Fix clicks during single-cycle DMA playback
